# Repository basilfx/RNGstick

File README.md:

# RNGstick
Entropy stick for experimenting, generating and evaluating true random numbers.

Status: evaluating prototype.

## Introduction
This project provides a hardware random number generation with a customizable firmware for experimenting. A NE555 free-running oscillator is used, of which the clock drift is measured and used as a source of randomness. The stick can be used for feeding the Linux entropy pool for random numbers.

The firmware is configurable via a built-in command line.

## Background
The idea for this project is from a research project I conducted during my master's programme. Together with two others, we did a research on using accelerometers from mobile phones for generating true random numbers.

### True randomness
True random numbers (in contrast to pseudorandom numbers) are unpredictable. Given a number, the next number is not predictable and not linked to it. Computers cannot generate true random numbers via an algorithm, but they can observe physical events and extract uncertainty (entropy). For instance, mouse movement, disk access time and network traffic times are considered unpredictable. There is one problem: these events may occur not frequent enough, which means that the pool of entropy will exhaust. For general purpose random numbers, this is not a big deal, but for generating cryptographic keys, this becomes a problem.

An operating system does not directly generate numbers from this pool, but uses a pseudorandom algorithm that is seeded with the collected entropy. On Linux, `/dev/random` will block when the entropy pool is exhausted, but `/dev/urandom` won't. A quick experiment is to `cat /dev/random` and move the mouse around. You will notice the rate of numbers will increase (at least on Linux without HWRNG).

### Project rationale
In the last few years, processor manufacturers have incorporated hardware random number generators in processors. A kernel can use this source directly to generate random numbers, or to feed the entropy pool. However, with recent NSA leakings, some OS's have already [announced](http://www.theregister.co.uk/2013/12/09/freebsd_abandoning_hardware_randomness/) to not trust these output sources directly.

This project is an open-source attempt to generate random numbers of sufficien quality, using a low number of hardware parts. It is based on [this](http://1474orchard.ca/projects/?x=entry:entry120926-185104) blog post, where the author is using a NE555 free-running oscillator and uses the clock drift as a source of randomness. An Arduino samples the output of the NE555 regularly, which is a point on the waveform. Clock drift is affected by temperature, part stability, voltage and many more factors, that are unpredictable in some sense. In short, given two waveforms they won't be the same as one period may be a tiny bit shorter or longer. Using hardware parts with more tolerance (thus more error) is preferred.

The next two graphs the P(x) values of the ADC sample distribution over the full ADC sample space (10 bits) and the bit distribution (again, 10 bits). Both graphs match the ones from the blog post. Note how the lower 5 bits are uniformly distributed.

I have used this design and created an USB stick with a customizable firmware for generating random bytes. In addition to the original design, the NE555 can be reset before each iteration (to target the same sample point) and the voltage reference for the ADC is customizable. Many parameters can be tuned to generate random numbers in a different way. The following features are available:

* Sampling: batch-samples, or per-sample
* Sample processing: masking, shifting and delays
* Bit extracting: one-majority, XOR, or raw bits
* Extraction: (Improved) Von Neumann bias removal, or none
* Generating: SHA-1, or none
* Bucketing: buffer bytes to output chuncks, or continuously
* Outputting: (Binary) bytes or bits

To give an idea of the output, the following distribution of the P-values was created, using ones-majority over the lower five bits and bias removal using Improved Von Neumann, without any generator. One should be careful to call the output random from this graph only, because a predictable sequence from 0-255 over and over would generate a similar graph.

More graphs can be found [here](https://github.com/basilfx/RNGstick/blob/master/docs/Graphs.md).

### Testing
The problem with random numbers is that you cannot prove they are random. However, there are statistical tests which can indicate if a sequence of random numbers is 'random' enough. Even a sequence of numbers that doesn't look random could be random, as the random number generator could produce this sequence.

Three programs are available to check the produced sequences. The first is `ent`, which calculates the Entropy, Chi-square Distribution and the Arithmetic Mean Value. The second one is `rngtest`, which implements the FIPS 140-2 tests. The last one is `dieharder`, which implements a lot of different tests.

Sidenote: SHA-1 will generate more bytes of randomness for one input byte. In some sense it is a pseudorandom algorithm. Given the internal state, the next output bytes can be predicted if the next input byte is predictable. Since SHA-1 is a computational strong hash function, it will most-certainly pass all statistical tests by default.

TODO add test results here

## Contents
* Eagle schematic and PCB
* Arduino firmware

## Eagle

### Bill of materials
| Part      | Value         | Device                    | Package         |
|-----------|---------------|---------------------------|-----------------|
|   C1      |   22pF        |   C-EUC0603K              |   C0603K        |
|   C2      |   22pF        |   C-EUC0603K              |   C0603K        |
|   C3      |   22pF        |   C-EUC0603K              |   C0603K        |
|   C4      |   22pF        |   C-EUC0603K              |   C0603K        |
|   C5      |   10nF        |   C-EUC0603K              |   C0603K        |
|   C6      |   100nF       |   C-EUC0603K              |   C0603K        |
|   C7      |   100nF       |   C-EUC0603K              |   C0603K        |
|   C8      |   100nF       |   C-EUC0603K              |   C0603K        |
|   D1      |               |   PESD5V0U1BB             |   SOD523        |
|   D2      |               |   PESD5V0U1BB             |   SOD523        |
|   IC1     |               |   NE555D                  |   SO08          |
|   JP1     |   USB-A-H     |   USB-A-H                 |   USB-A-H       |
|   JP4     |   M02PTH      |   M02PTH                  |   1X02          |
|   R1      |   5K          |   TRIM_EU-3223W           |   3223W         |
|   R2      |   330R        |   R-EU_R0603              |   R0603         |
|   R3      |   10k         |   R-EU_R0603              |   R0603         |
|   R4      |   10k         |   R-EU_R0603              |   R0603         |
|   U2      |               |   CH340G                  |   SOIC16        |
|   U1      |               |   ATMEGA328               |   TQFP32-08     |
|   Q1      |   16MHz       |   MT-OSCILLATOR           |   MT            |
|   Q2      |   12MHz       |   MT-OSCILLATOR           |   MT            |

### Board render
Render of the stick. It measures 1.45x0.65 inch.

## Firmware
The firmware resides in `firmware/RNG`. You will need a copy of the [CommandLine](https://github.com/basilfx/Arduino-CommandLine) library and the [Cruiptosuit](https://github.com/spaniakos/Cryptosuite/) library.

Modify the `Arduino/CommandLine/CommandLine.h` file to reflect the following (see its `README.md` file why):

```
#define COMMANDLINE_COUNT 24
#define COMMANDLINE_BUFFER 24
// #define COMMANDLINE_PRE_POST
#define COMMANDLINE_HISTORY 0
```

## Software

### Configuration
To configure the stick, short JP4 while booting. A setup prompt should appear. Use the `help` command to list all available commands. Do not forget to save a change using the `save` command. Use `defaults` or `load` respectively.

### Installation
This will install `rng-tools` for feeding the random numbers back into the kernel. It applies to Ubuntu 15.04, but others will work fine too. `/dev/ttyACM0` is assumed to be the RNGstick.

* Instal `rng-tools` via `sudo apt-get install rng-tools`
* Change `/etc/defaults/rng-tools`
 * Add `stty -F /dev/ttyACM0 115200 time 25`
 * Add `HRNGDEVICE=/dev/ttyACM0`
* Restart `rng-tools` with `sudo service rng-tools restart`
* Observe `/proc/sys/kernel/random/entropy_avail`

## License
See the `LICENSE` file (MIT license).

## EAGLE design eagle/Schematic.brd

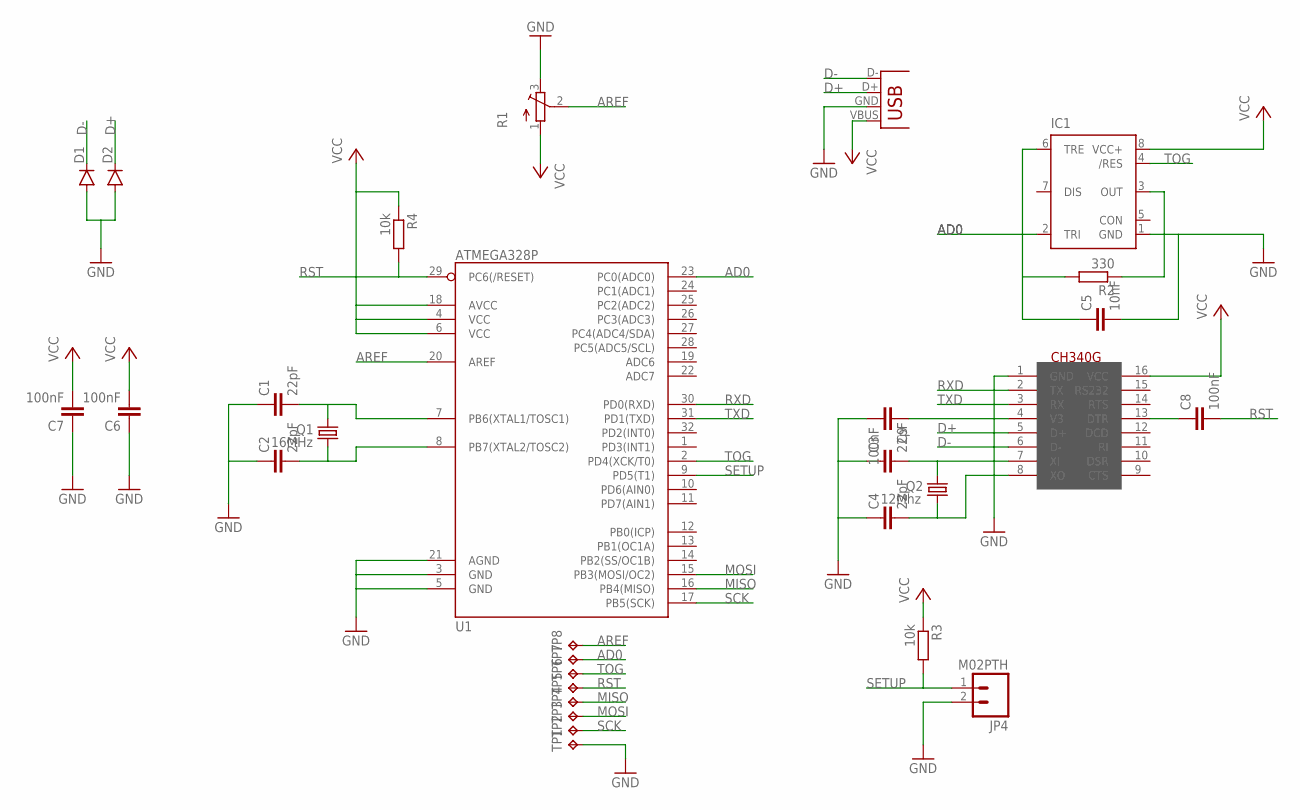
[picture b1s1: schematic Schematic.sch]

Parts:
C1, C2, C3, C4: 22pF; C0603K
C5: 10nF; C0603K
C6, C7, C8, C9: 100nF; C0603K
D1, D2: DIODESOD523; SOD523
IC1: NE555D; SO08
JP1: USB-A-H
JP4: M02PTH; 1X02
Q1: 16MHz; MT
Q2: 12Mhz; MT
R1: TRIM_EU-3223W; 3223W
R2: 330; R0603
R3, R4: 10k; R0603
TP1, TP2, TP3, TP4, TP5, TP6, TP7, TP8: TPTP10R; TP10R
U1: ATMEGA328P; TQFP32-08
U2: CH340G; SOIC16

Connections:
AD0: C5.1, IC1.2 (TRI), IC1.6 (TRE), R2.2, TP7.TP, U1.23 (PC0(ADC0))
AREF: R1.2 (S), TP8.TP, U1.20 (AREF)
D+: D2.C, JP1.D+ (D-), U2.5 (D+)
D-: D1.C, JP1.D- (D+), U2.6 (D-)
GND: C1.1, C2.1, C3.1, C4.1, C5.2, C6.1, C7.1, C9.2, D1.A, D2.A, IC1.1 (GND), JP1.GND (VBUS), JP4.2, R1.3 (E), TP1.TP, U1.3 (GND), U1.5 (GND), U1.21 (AGND), U2.1 (GND)
MISO: TP4.TP, U1.16 (PB4(MISO))
MOSI: TP3.TP, U1.15 (PB3(MOSI/OC2))
unnamed: IC1.3 (OUT), R2.1
unnamed: C3.2, Q2.3 (2), U2.7 (XI)
unnamed: C4.2, Q2.1, U2.8 (XO)
unnamed: C1.2, Q1.3 (2), U1.7 (PB6(XTAL1/TOSC1))
unnamed: C2.2, Q1.1, U1.8 (PB7(XTAL2/TOSC2))
unnamed: C8.1, U2.13 (DTR)
unnamed: C9.1, U2.4 (V3)
RST: C8.2, R4.2, TP5.TP, U1.29 (PC6(/RESET))
RXD: U1.30 (PD0(RXD)), U2.2 (TX)
SCK: TP2.TP, U1.17 (PB5(SCK))
SETUP: JP4.1, R3.2, U1.9 (PD5(T1))
TOG: IC1.4 (/RES), TP6.TP, U1.2 (PD4(XCK/T0))
TXD: U1.31 (PD1(TXD)), U2.3 (RX)
VCC: C6.2, C7.2, IC1.8 (VCC+), JP1.VBUS (GND), R1.1 (A), R3.1, R4.1, U1.4 (VCC), U1.6 (VCC), U1.18 (AVCC), U2.16 (VCC)

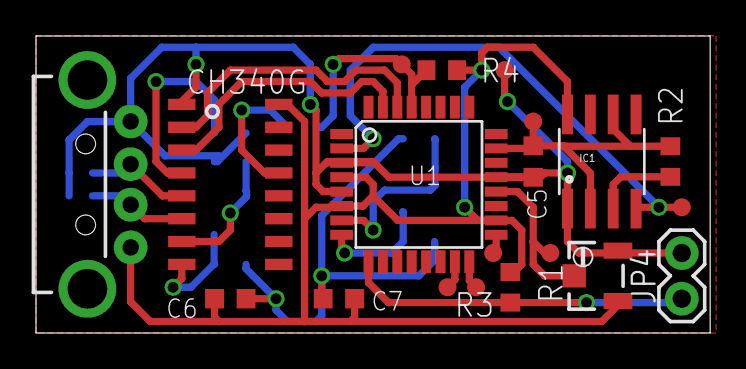
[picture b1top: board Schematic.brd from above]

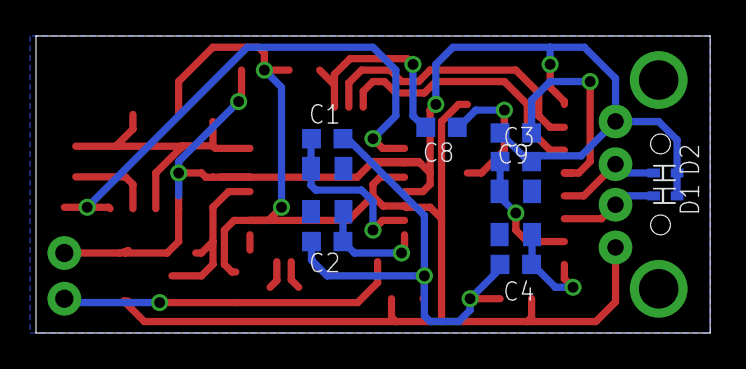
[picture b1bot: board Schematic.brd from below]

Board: 2 copper layers, 37.5 x 16.5 mm, 30 parts (10 on the bottom side), 21 nets.

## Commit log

2015-05-09 Initial commit.
2015-05-10 Updated README.
2015-05-10 Added sample bucket and XOR.
2015-05-10 Add test runner.
2015-05-10 Added DTR reset, converted XTAL to smaller ones.
2015-05-10 Converted strings to PROGMEM to save memory. Tweak buckets for maximal memory usage.
2015-05-10 Improved testrunner.
2015-05-12 Added more graphs of distributions.
2015-05-12 Bugfix in limits.
2015-05-12 Fix links.
2015-08-02 Reduce sample size. 256kb will take ages.
2015-08-02 Adapt code to reflect the new CommandLine library.
2015-08-02 Updated README.md for new CommandLine library.
2017-12-12 Fix output mode command.
2017-12-12 Add error helper.
2017-12-13 Fix PCB errors after first prototype.
2024-07-08 Rework contrib

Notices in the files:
parts and their libraries:
SparkFun-AnalogIC: Licensing:Creative Commons ShareAlike 4.0 International - https://creativecommons.org/licenses/by-sa/4.0
